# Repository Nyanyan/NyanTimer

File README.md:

# NyanTimer
DIY Stackmat Timer for cubing

**日本語は下部にあります。**

<!-- TOC -->

- [NyanTimer](#nyantimer)
    - [Abstract](#abstract)
    - [Functions](#functions)
    - [概要](#概要)
    - [機能](#機能)
    - [使い方](#使い方)
        - [電池](#電池)
        - [電源](#電源)
        - [ボタン](#ボタン)
        - [タイマースタート・ストップ](#タイマースタート・ストップ)
        - [インスペクションタイム計測](#インスペクションタイム計測)
        - [ラップタイム計測](#ラップタイム計測)
        - [ハック](#ハック)
            - [board-v7でのハック](#board-v7でのハック)
        - [NyanTimerライブラリ](#nyantimerライブラリ)
            - [入手](#入手)
            - [必要なライブラリ](#必要なライブラリ)
            - [関数で使用する定数と変数](#関数で使用する定数と変数)
                - [NyanTimerの各ピン](#nyantimerの各ピン)
                - [基礎的な変数](#基礎的な変数)
            - [関数の紹介](#関数の紹介)
    - [開発環境](#開発環境)
    - [技術的な解説](#技術的な解説)
        - [ハードウェア](#ハードウェア)
            - [ボディ](#ボディ)
            - [タッチセンサ](#タッチセンサ)
            - [その他の入出力部品](#その他の入出力部品)
        - [ソフトウェア](#ソフトウェア)
            - [全体的な処理](#全体的な処理)
            - [信号](#信号)
    - [ファイル](#ファイル)
        - [board](#board)
        - [body](#body)
        - [program](#program)
        - [README](#readme)
    - [参考資料](#参考資料)

<!-- /TOC -->

## オープンソースバージョンの使い方

### 電池

左右にある写真の蓋を取って、CR2450を入れます。

ちょっと蓋が取りにくいです。裏側に出ているネジを押しつつ表側でネジの上を押さえると取りやすいです。

### 電源

タイマーにあるスライドスイッチで電源が入ります。これも少し扱いにくいです(ごめんなさい)

秋月にいい感じのスイッチが見当たらなくて…

### ボタン

* 左上: インスペクションタイム計測モード切り替え

* 左下: タイムリセット

* 右上: ラップ計測回数調整(アップ)

* 右下: ラップ計測回数調整(ダウン)

### タイマースタート・ストップ

manualをご覧ください。

### インスペクションタイム計測

manualをご覧ください。

### ラップタイム計測

manualをご覧ください。

### ハック

manualをご覧ください。

### NyanTimerライブラリ

manualをご覧ください。

## 開発環境

Visual Studio Code

Arduino IDE

Autodesk Eagle

Autodesk Fusion 360

## 技術的な解説

### ハードウェア

基板について詳しいことはboard-vXの中のEagleのデータをご覧ください(回路図描くのが下手でごめんなさい)。簡単に説明すると、Arduinoから各部品に接続しているだけです。

ボディとタッチセンサについてのみ、少し細かく説明をします。その後、その他の部品の概要を少し書きます。

####  ボディ

ボディはAutodesk Fusion 360で設計し、CNCフライス盤で切り出しました ~~(今後レーザーカッターでの出力に方針転換する予定)~~  今後は3Dプリンタで試作した後、金型作って大量生産する予定です。

#### タッチセンサ

スタックタイマーのタッチセンサは静電容量方式のセンサです。これについて、今回は自作しました。

少々図が汚いですが勘弁してください。

この図でP$1となっているところがタッチパッドの部分です。PADLINから5Vを定期的に入れて、PADLにかかる電圧を調べます。この時、タッチパッドに手を置いているとタッチパッドと手とがそれぞれ極板となって擬似的なコンデンサが成立し、このコンデンサを充電することになります。そのためにPADLがHIGHになるまでの時間が延び、タッチパッドに手が置かれたことを判定できます。

詳しい静電容量方式のセンサについては以下を参照してください。

https://www.fujiele.co.jp/semiconductor/ti/tecinfo/news201707210000/

http://nn-hokuson.hatenablog.com/entry/2017/03/22/200454

なお、電池が多少減ってきても正確にタッチセンサが動くよう、電源投入時にPADLにかかる電圧を測定し、それに1未満の係数を掛けた値をPADLがHIGHであると判定する閾値にしました。

余談ですが、キューブの大会ではタイマーで1/1000秒まで計測可能であるにも関わらず、公式タイムには1/100秒までしか書きません。この理由を私は詳しく知りませんが、このセンサの「時間を計測することで近接を感知する」特性によるところもあるのではないかと個人的に思っています。

#### その他の入出力部品

ブザー

タクトスイッチ

液晶(16文字x2行)

### ソフトウェア

#### 全体的な処理

なぜか繰り返し記号が使えなかったので適当に六角形で代用です。

プログラム中では左側がbutton()で、右側がtimer()です。

これ以外にも色々複雑に処理はしていますが、まあ大体はこんな感じです。

マイコンは要するにArduinoなので、使えるタイマーはTimer1とTimer2の２つのみです。そのため、Timer2は信号の割り込み処理にずっと使うとして、時間計測とインスペクションタイム計測をTimer1でやっています。

#### 信号

信号はこちらなどを参考にしました。

https://github.com/fw42/atmel/tree/master/stackmat

簡単に日本語で書きます。私は通信には詳しくないので、正確には上を参照してください。

* 信号はRS232
* 1200bps
* データビットは8つ(ステータス、時刻、チェックサム)
* パリティビットなし
* 終了ビットは一つ(LF)

送るデータ

* 1: ステータスのデータ('I', 'A', 'S', 'L', 'R', 'C', ' ')
* 2-7: 時刻のデータ(1:23.45なら‘12345’)
* 8: チェックサム(ASCIIコードで64+タイムの各数字の和, 上の例ならASCIIで79=O)
* 9: CR(ASCIIコード0x0D)
* 10: LF(ASCIIコード0x0A)

1番目、ステータスのデータは、

* ‘I’: タイマー初期化(リセットされた状態)
* ‘A’: タイマースタート直前(パッドを手で押さえて、話したらスタートできる状態)
* ‘ ’: 計測中
* ‘S’: タイム計測完了
* ‘L’: 左パッドが覆われている状態
* ‘R’: 右パッドが覆われている状態
* ‘C’: 両方のパッドが覆われている状態

ただし、NyanTimerでは‘C’は特に必要ないために実装していません(以前は‘R’,‘L’も実装していませんでしたが、CS Timerのインスペクションタイム計測機能であると便利とわかり実装しました)。

## ファイル

### board

基板です。2019/09/05現在、v4-v7までのボードの動作確認がとれています。

### body

外装

Fusion360のファイルとobjとstlファイル

body-v2内のncファイルはPartsTogether内のが最新版です

### program

プログラムとライブラリ

~~中に“calibration”とついたものがありますが、これはタッチセンサで電源投入時に自動でキャリブレーションを行うプログラムです。2019/09/24現在キャリブレーションは試用の機能なので分けて開発しています(Gitを使いこなせていない)~~

2019/10/11追記: キャリブレーション機能はデフォルトの機能になりました。古いプログラムは“archive”内に移動しました。

~~“withfunc”のついたプログラムは、NyanTimer専用関数郡を別に書いたもので、2019/10/11現在試用のプログラムです。~~ 2019/10/14現在、デフォルトのプログラムになりました。

### README

これ

## 参考資料

信号関係(私がまとめた日本語記事): https://qiita.com/Nyanyan_Cube/items/e517e71cf5c4e2aaf1e5

信号関係(英語記事): https://github.com/fw42/atmel/tree/master/stackmat

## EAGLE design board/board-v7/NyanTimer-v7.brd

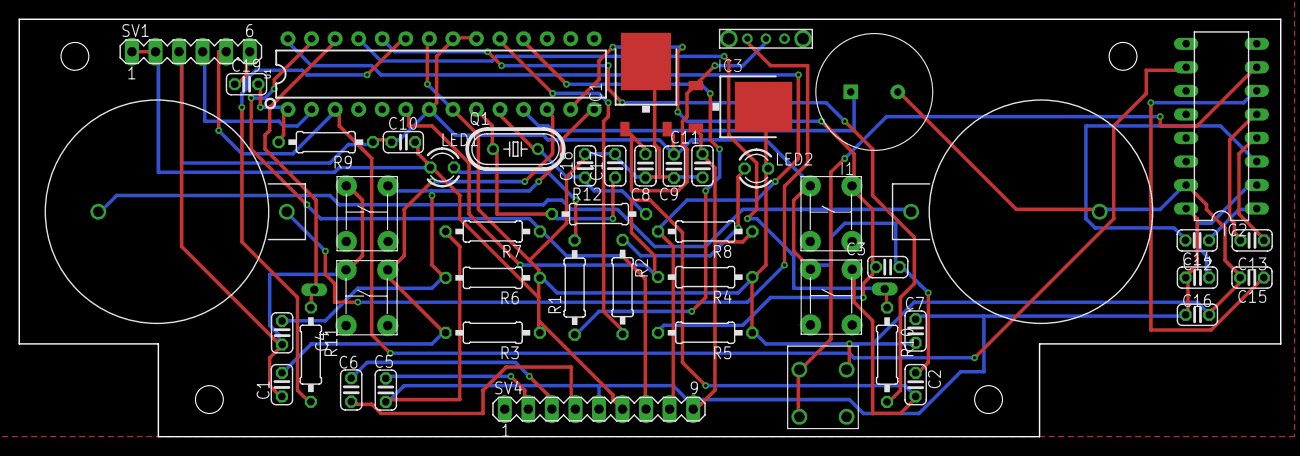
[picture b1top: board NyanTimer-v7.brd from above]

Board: 2 copper layers, 136.0 x 45.0 mm, 51 parts (0 on the bottom side), 37 nets.

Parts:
BT1, BT2: AKIZUKI_CR2032
C1, C2, C3, C4, C7, C8, C10, C12, C13, C14, C15, C16, C19: 0.1u; C025-024X044
C5, C6: 1u; C025-024X044
C9, C11: 2.2u; C025-024X044
C17, C18: 22p; C025-024X044
CONNECTOR1, CONNECTOR2, CONNECTOR3, CONNECTOR4: TACT_SWITCH
I1: P-04118_PKM13EPYH4000; PKM13EPYH4000
IC1, IC3: 7815DT; TO252
IC2: MAX232; DIL16
LED1, LED2: LED3MM
PHN1: PHONE
PIN1, PIN2: 1PINHEAD
Q1: HC49/S
R1, R2: 220; 0207/10
R3, R4, R5, R6, R7, R8, R9: 10k; 0207/10
R10, R11: 10M; 0207/10
R12: 1M; 0207/10
SV1: MA06-1
SV4: MA09-1
SW1: AKIZUKI_SWITCH
U1: 328P; DIP28

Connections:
+5V: C1.1, C2.1, C3.1, C4.1, C9.1, C10.1, CONNECTOR1.3, CONNECTOR2.3, CONNECTOR3.3, CONNECTOR4.3, IC1.2, R9.1, SV1.3, U1.7, U1.20, U1.21
BUZ+: I1.1, U1.11
GND: BT2.MINUS, C7.1, C8.2, C9.2, C10.2, C11.2, C15.2, C16.2, C17.2, C18.2, I1.2, IC1.3, IC2.15, IC3.3, LED1.K, LED2.K, PHN1.GND, R3.1, R4.1, R5.1, R6.1, SV1.1, SV1.2, SV4.6, U1.8, U1.22
LEDG: R2.1, U1.19
LEDR: R1.1, U1.18
unnamed: LED1.A, R1.2
unnamed: LED2.A, R2.2
unnamed: C5.2, SV4.2
unnamed: C6.1, SV4.4
unnamed: C6.2, SV4.3
unnamed: C19.1, SV1.6
unnamed: BT1.MINUS, BT2.PLUS
unnamed: C12.2, IC2.3
unnamed: C12.1, IC2.1
unnamed: C13.1, IC2.4
unnamed: C13.2, IC2.5
unnamed: C14.2, IC2.2
unnamed: C15.1, IC2.6
PADL: PIN1.P$1, R11.1, U1.26
PADLIN: R11.2, U1.23
PADR: PIN2.P$1, R10.1, U1.25
PADRIN: R10.2, U1.24
PHONE: IC2.7, PHN1.PIN1, PHN1.PIN3
RESET: C19.2, R9.2, U1.1
RX: SV1.4, U1.2
S1: C17.1, Q1.1, R12.1, U1.9
S3: C18.1, Q1.2, R12.2, U1.10
SCL: R8.2, SV4.8, U1.28
SDA: R7.2, SV4.7, U1.27
SW1: C1.2, CONNECTOR1.4, R3.2, U1.12
SW2: C2.2, CONNECTOR2.4, R4.2, U1.6
SW3: C3.2, CONNECTOR3.4, R5.2, U1.13
SW4: C4.2, CONNECTOR4.4, R6.2, U1.14
T2IN: IC2.10, SV1.5, U1.3
VCC: C5.1, C7.2, C11.1, C14.1, C16.1, IC2.16, IC3.2, R7.1, R8.1, SV4.5, SV4.9
VSW: BT1.PLUS, SW1.PIN1
VSWOUT: C8.1, IC1.1, IC3.1, SW1.PIN2

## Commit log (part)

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2019-09-23 modified threshold if
2019-09-23 fixed bug
2019-09-23 adjust threshold
2019-09-23 modified threshold
2019-09-23 calibration
2019-09-23 calibration modified
2019-09-23 modify threshold
2019-09-23 ban outmode
2019-09-23 fixed
2019-09-23 changed to outmode
2019-09-23 fixed lap bug
2019-09-23 fixed start bug
2019-09-24 modified power on touch voltage
2019-09-24 modified filed
2019-09-24 modified readme
2019-09-25 created board-v7
2019-09-25 modified
2019-09-25 modified padl pin
2019-09-25 routed
2019-09-25 created garber
2019-09-25 created body-v2 folder
2019-09-25 renamed
2019-09-25 add body-v2 files
2019-09-26 deleted GTS
2019-09-26 mounted USB-Serial pinhead
2019-09-26 changed pad
2019-09-26 beta
2019-09-26 deleted garber
2019-09-26 mistake
2019-09-26 modified & made garber
2019-09-26 modfied 3d models
2019-09-28 light LED while inspection time
2019-10-02 modfied nc
2019-10-02 fasten
2019-10-03 modified readme: board v7
2019-10-03 archived some programs
2019-10-04 deleted unuseful things
2019-10-04 modified name
2019-10-04 made nyantimer lib
2019-10-04 modified files
2019-10-04 modified lib
2019-10-04 modified lib and program
2019-10-04 modified lu\ib
2019-10-04 not working
2019-10-05 work?
2019-10-05 worked
2019-10-05 dont work
2019-10-05 worked!!!!
2019-10-05 moved lib
2019-10-05 deleted lib
2019-10-05 modified program
2019-10-05 added lib
2019-10-06 lib timer
2019-10-06 modified program: lib timer
2019-10-06 modified lib: timer
2019-10-06 modified led
2019-10-06 modified lib & pro
2019-10-06 give up making lib
2019-10-07 decide to make lib
2019-10-08 work...
2019-10-08 updated libs
2019-10-08 updated lib and program
2019-10-08 updated lib
2019-10-09 give up making lib, and use functions
2019-10-09 modified lib modoki
2019-10-09 modified signalOut and around
2019-10-10 added body-v3
2019-10-10 modified readmme
2019-10-11 modified stl
2019-10-12 deleted body v3
2019-10-13 added image
2019-10-13 modified img
2019-10-13 dont work externs
2019-10-13 char to str
2019-10-13 modified program: inputButton
2019-10-14 archived
2019-10-15 modified board
2019-10-15 Created license
2019-10-20 added drawing
2019-10-25 updated drawing
2019-10-25 added how2use
2019-10-25 modified manual
2019-10-25 added svg
2019-10-29 modified lib: padXinthreshold
2019-10-30 mocified manual
2019-11-05 fixed button bug
2019-11-05 refact
2019-11-05 auto-power-off
2019-11-05 auto power off works
2019-11-05 display memory
2019-11-05 deleted memory print
2019-11-07 soundmode
2019-11-07 soundmode work
2019-11-07 sound mode fin
2019-11-07 modified readme and manual
2019-11-08 buzzing alert when +2 and DNF
2019-11-09 test commit readme modified
2019-11-10 touch modified
2019-11-17 modified timer start
2019-11-17 modified lap measurement
2019-11-17 modified touch
2019-11-17 worked!!
2019-11-17 modified formertouch
2019-11-17 give up lap with one hand
2019-11-18 oh touch lap
2019-11-18 chatering
2019-11-18 added num
2019-11-19 addded img and modified manual
2019-11-20 deleted comments
2019-11-24 deleted
2019-11-24 deleted unused num
2019-11-25 modified program and readme
2019-11-25 modified docs
2019-11-25 modified prgram: lapout
2019-11-26 modified libs
2019-11-26 dont reset time if power off without reset
2019-11-27 modified img and manual
2019-11-27 modfied manual
2019-11-27 modified manual and readme
2019-12-01 modified program: calib
2019-12-15 Update LICENSE
2020-01-07 finish debug
2020-01-16 changed dir
2020-01-16 ignore
2020-01-16 deleted script
2020-01-16 make file and sample program
2020-01-16 dont \n when scramble[i] in adds
2020-01-16 mount start and stop
2020-01-16 mount timing
2020-01-16 save time
2020-01-16 ao5 and ao12, bests
2020-01-16 best single
2020-01-16 status
2020-01-16 status: ao50,100,1000
2020-01-16 ao50 and ao1000
2020-01-16 modified ao50/100
2020-01-16 added data files
2020-01-16 index and del
2020-01-16 setup
2020-01-17 change session
2020-01-17 mount func of change session
2020-01-17 scramble
2020-01-17 fix bug
2020-01-25 fixed session change bug
2020-01-25 calc time aox list
2020-01-25 TBD view time
2020-01-25 modified scramble
2020-01-25 padding
2020-01-25 view time
2020-01-27 view time modified
2020-01-27 deleted comment
2020-01-31 show time during time list
2020-02-01 banned waiting threshold, use millis()
2020-02-04 arduino program
2020-02-05 TBD mounting serial
2020-02-05 debugging
2020-02-05 TBD calctime
2020-02-06 serial fin
2020-03-01 rm TNoodle
2020-03-30 inspection TBD
2020-03-30 TBD record inspection time
2020-03-30 DONE record inspection time
2020-03-31 sound
2020-03-31 sound DNE
2020-03-31 mount +2 and DNF TBD
2020-03-31 fixing bug TBD
2020-03-31 auto shutdown
2020-04-21 modified nyantimer2
2020-05-04 added comment
2020-05-04 input_pullup
2020-07-11 refactaring
2020-08-25 program
2020-10-18 nyantimer3

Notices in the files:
parts and their libraries:
SparkFun-IC-Microcontroller: Licensing: Creative Commons ShareAlike 4.0 International - https://creativecommons.org/licenses/by-sa/4.0
